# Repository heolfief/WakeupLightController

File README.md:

# WakeupLightController
**[THIS IS AN ABORTED WORK (lack of time to finish it)]**

This is a credit-card sized board designed to control LEDs (for example LED strip) as a wake-up light.

## What it does
The controller function in two modes :
* **Fade lamp**, LED intensity is controlled by an external potentiometer
* Parametric Progressive **wake-up light**

Wake-up times can be set by the dedicated **bluetooth android app**, and can be set for the week.
For example you can set the light to wake you up at half past 8 on Monday and at 12 on Sunday.

You can **enable or disable alarm** for **each day** with the app, or you can **manually disable all alarms** with an external **switch**.

When a alarm time approaches, the lamp will start to **fade-in linearly** and will be at **full intensity** when alarm time is reached.
The **duration** of the fade-in **can be set** via the app.

The board will **keep alarm settings** until new one are set, **even if power goes down**.

## How it works

The board is based on an **AVR microcontroller** (ATmega328p), a **bluetooth serial module** (HC-05), and a **real time clock** (DS3231).
The MCU is programmed in **C** within the **Atmel Studio 7** environment.

The real time clock is **extremely acurate** and will only drift few second per year. It is used to keep track of time to trigger alarms.

The bluetooth module is used to **pair an android device** with the board, and to send and get settings from a user.

The programm is composed of a main **state machine** and **run by interrupts**.

The **LED intensity** is controlled by a **16bits PWM**. As the ADC is only 10bits, when using the board as a lamp with a potentiommeter, LED intensity will only be controlled with a 10 bit resolution. That mean it as **1024 intensity steps** which is enough for most applications. However, when using the wake-up function, the LED intensity will be controlled by a 16bit resolution (**65536 steps**) which is good for a **very slow fade**.

**Brightness intensity** is **automaticaly compensated** to be seen as **linear by the human eye**.

**Settings are kept** even if power goes off by writing them to the **EEPROM**.

## Wiring

#### What you will need to connect to the board :
* A **12v** power source capable to deliver current for your LED setup + 200mA (max) for the board.
* **LEDs**, for example an LED strip. The board is thermally capable of delivering up to **4A** of current.
* A **potentiometer** (1 to 100k linear). You can use a rotary or a linear one.
* A **momentary button** for bluetooth pairing.  
* A **switch** if you want to add a way to manualy disable all alarms (even if they are enabled by the app).

Connection to the board are made by screwing cables to the screw terminals following this pinout diagram :

#### List of pins
* **GND**: Ground (0V) connection
* **+12V in**: Input for the 12V power source
* **+5V out**: Output to connect to pin 3 of potentiometer
* **POT**: Potentiometer wiper (pin 2) input
* **GND**: Ground (0V) connection for pin 1 of potentiometer
* **LED +**: LED anode (+) connection
* **LED -**: LED cathode (-) connection
* **Alarm sw.**: Switch input (switch connect the input to GND when turned on, floating when off) for disabling alarms
* **Pair/stop bt.**: Bluetooth pairing and alarm stop button (button connect the input to GND when turned on, floating when off)

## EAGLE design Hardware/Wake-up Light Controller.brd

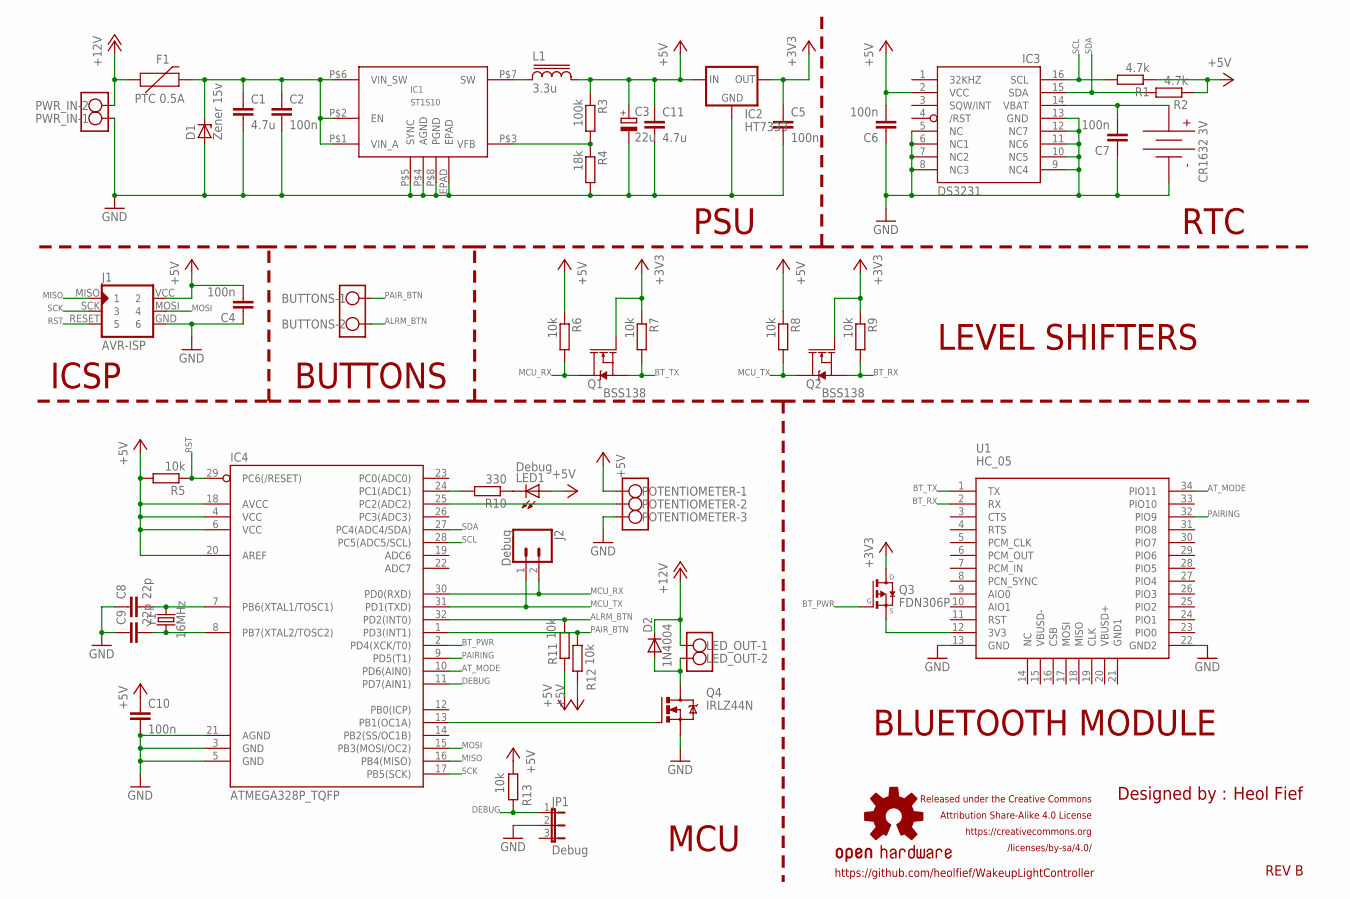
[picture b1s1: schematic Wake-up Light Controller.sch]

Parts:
BUTTONS: W237-102
C1, C11: 4.7u; C0805
C2, C4, C5, C6, C7, C10: 100n; C0805
C3: 22u; 153CLV-0405
C8, C9: 22p; C0805
D1: Zener 15v; SOD80C
D2: 1N4004; DO-214AC
F1: PTC 0.5A; PTH
IC1: ST1S10
IC2: HT7333; SOT-89
IC3: DS3231/SO; SO16W
IC4: ATMEGA328P_TQFP; TQFP32-08
J1: AVR-ISP; AVR-ISP-6PIN-SMAILL-SILK
J2: Debug; 1X02_NO_SILK
J3: CR1632_3V; BATTCON_16MM_PTH
JP1: Debug; JP2
L1: 3.3u; 74437346068
LED1: Debug; CHIPLED_1206
LED_OUT: W237-102
LOGO1: OSHW-LOGOM-COPPER; OSHW-LOGO-M_COPPER
POTENTIOMETER: W237-103
PWR_IN: W237-102
Q1, Q2: BSS138; SOT23-3
Q3: FDN306P; SSOT-3
Q4: IRLZ44N; TO220BH
R1, R2: 4.7k; M0805
R3: 100k; M0805
R4: 18k; M0805
R5, R6, R7, R8, R9, R11, R12, R13: 10k; M0805
R10: 330; M0805
U1: HC_05; BLUETOOTH_SMD
Y1: 16MHz; CRYSTAL-SMD-3.2X2.5MM

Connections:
+3V3: C5.1, IC2.1 (OUT), Q1.1 (G), Q2.1 (G), Q3.3 (D), R7.1, R9.1
+5V: C3.+, C4.2, C6.2, C10.1, C11.1, IC2.3 (IN), IC2.4 (IN), IC3.2 (VCC), IC4.4 (VCC), IC4.6 (VCC), IC4.18 (AVCC), IC4.20 (AREF), J1.VCC (2), L1.2, LED1.A, POTENTIOMETER.1, R1.1, R2.1, R3.1, R5.2, R6.1, R8.1, R11.1, R12.1, R13.2
+12V: D2.C, F1.P$1 (1), LED_OUT.1, PWR_IN.2
ALRM_BTN: BUTTONS.2, IC4.32 (PD2(INT0)), R11.2
AT_MODE: IC4.10 (PD6(AIN0)), U1.34 (PIO11)
BT_PWR: IC4.2 (PD4(XCK/T0)), Q3.1 (G)
BT_RX: Q2.2 (S), R9.2, U1.2 (RX)
BT_TX: Q1.2 (S), R7.2, U1.1 (TX)
DEBUG: IC4.11 (PD7(AIN1)), JP1.1, R13.1
GND: C1.2, C2.2, C3.-, C4.1, C5.2, C6.1, C7.1, C8.1, C9.1, C10.2, C11.2, D1.A, IC1.EPAD, IC1.P$4 (AGND), IC1.P$5 (SYNC), IC1.P$8 (PGND), IC2.2 (GND), IC3.5 (NC), IC3.6 (NC1), IC3.7 (NC2), IC3.8 (NC3), IC3.9 (NC4), IC3.10 (NC5), IC3.11 (NC6), IC3.12 (NC7), IC3.13 (GND), IC4.3 (GND), IC4.5 (GND), IC4.21 (AGND), J1.GND (6), J3.GND, JP1.2, POTENTIOMETER.3, PWR_IN.1, Q4.S, R4.2, U1.13 (GND), U1.22 (GND2)
MCU_RX: IC4.30 (PD0(RXD)), J2.2, Q1.3 (D), R6.2
MCU_TX: IC4.31 (PD1(TXD)), J2.1, Q2.3 (D), R8.2
MISO: IC4.16 (PB4(MISO)), J1.MISO (1)
MOSI: IC4.15 (PB3(MOSI/OC2)), J1.MOSI (4)
unnamed: D2.A, LED_OUT.2, Q4.D
unnamed: C8.2, IC4.7 (PB6(XTAL1/TOSC1)), Y1.3 (2)
unnamed: IC4.24 (PC1(ADC1)), R10.2
unnamed: C9.2, IC4.8 (PB7(XTAL2/TOSC2)), Y1.1
unnamed: Q3.2 (S), U1.12 (3V3)
unnamed: IC1.P$7 (SW), L1.1
unnamed: IC1.P$3 (VFB), R3.2, R4.1
unnamed: LED1.C, R10.1
unnamed: C1.1, C2.1, D1.C, F1.P$2 (2), IC1.P$1 (VIN_A), IC1.P$2 (EN), IC1.P$6 (VIN_SW)
unnamed: IC4.13 (PB1(OC1A)), Q4.G
unnamed: IC4.25 (PC2(ADC2)), POTENTIOMETER.2
PAIRING: IC4.9 (PD5(T1)), U1.32 (PIO9)
PAIR_BTN: BUTTONS.1, IC4.1 (PD3(INT1)), R12.2
RST: IC4.29 (PC6(/RESET)), J1.RESET (5), R5.1
SCK: IC4.17 (PB5(SCK)), J1.SCK (3)
SCL: IC3.16 (SCL), IC4.28 (PC5(ADC5/SCL)), R1.2
SDA: IC3.15 (SDA), IC4.27 (PC4(ADC4/SDA)), R2.2
VBAT: C7.2, IC3.14 (VBAT), J3.VCC@1 (VCC), J3.VCC@2 (VCC)

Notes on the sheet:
PSU
ICSP
MCU
REV B
Heol Fief
Designed by :
Released under the Creative Commons Attribution Share-Alike 4.0 License https://creativecommons.org /licenses/by-sa/4.0/
BLUETOOTH MODULE
RTC
BUTTONS
LEVEL SHIFTERS
CR1632 3V
https://github.com/heolfief/WakeupLightController

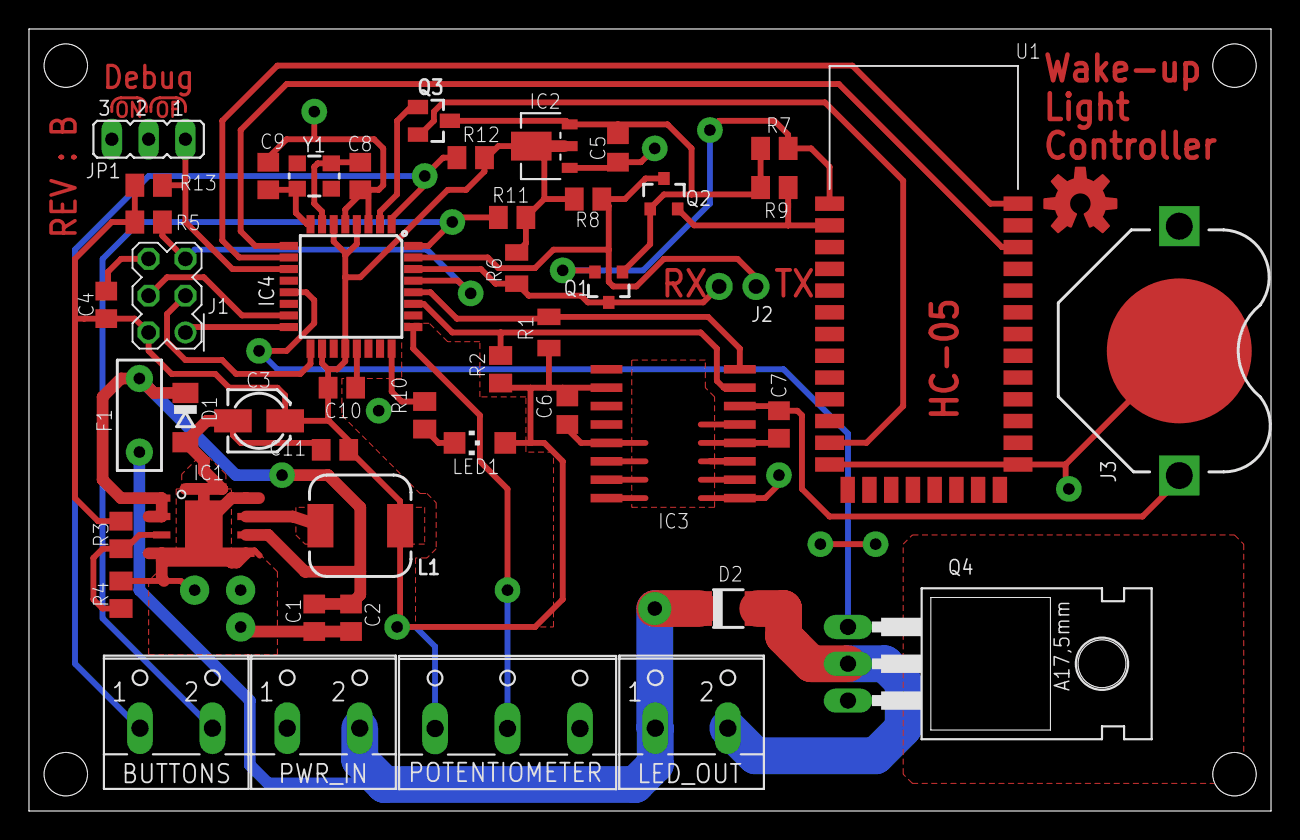
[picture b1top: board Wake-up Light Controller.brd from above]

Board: 2 copper layers, 85.7 x 54.0 mm, 48 parts (0 on the bottom side), 32 nets.

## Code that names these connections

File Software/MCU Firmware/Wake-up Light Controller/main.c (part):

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
// Hardware related constants//////////////////////////////
#define F_CPU			16000000UL						// 16MHz external oscillator
#define BT_PWR			PD4								// ...
#define AT_MODE			PD6								// ...
#define ALRM_BTN		PD2								// ...
#define PAIR_BTN		PD3								// ...
#define PAIR_INFO		PD5								// ...
#define DEBUG_JUMPER	PD7								// ...
#define DEBUG_LED		PC1								// ... Define IOs

// Software related constants//////////////////////////////
#define ALRM_EN			1								// ...
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
// User definable constants///////////////////////////////
#define PAIR_NAME	"Wake up light"						// Name of the bluetooth device, change it to whatever you like (Max 20 characters)
#define PAIR_PIN	"1234"								// Password of the bluetooth device pairing, change it to whatever you like
#define OFFTHRESHOLD 2									// Threshold (10 bit value) for potentiometer to be read as 0 (lamp off) to compensate for noise

// Libraries used/////////////////////////////////////////
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	DDRD &= ~((1<<PAIR_INFO) | (1<<ALRM_BTN));			// PAIR_INFO and ALRM_BTN as inputs
	DDRD |= (1<<BT_PWR) | (1<<AT_MODE);					// BT_PWR and AT_MODE as outputs
	DDRD &= ~((1<<ALRM_BTN) | (1<<PAIR_BTN) | (1<<DEBUG_JUMPER));// Alarm and pair buttons as inputs, debug jumper as input
	DDRB |= (1<<PB1);									// PB1 (OSC1A) as output
	PORTC |= (1<<DEBUG_LED);							// DEBUG_LED off
	PORTD |= (1<<BT_PWR);								// High level (BT module off)
	PORTD &= ~(1<<AT_MODE);								// Low level
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	PORTD |= (1<<ALRM_BTN) | (1<<PAIR_BTN) | (1<<DEBUG_JUMPER);	// Enable (weak) internals pullups

	PCICR |= (1<<PCIE2);								// Enable pin change interrupts
	PCMSK2 |= (1<<PCINT21);								// Enable pin change interrupt 21 (connected to pairing pin of bluetooth module)

	EIMSK |= (1<<INT1);									// Enable external interrupt INT1
	EICRA |= (1<<ISC11);								// ...
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	UART_transmit_String("\r\n");						// Send carriage return and new line

	UART_transmit_String("AT+PSWD=");					// ...
	UART_transmit_String(PAIR_PIN);						// ... Change the bluetooth pairing password
	UART_transmit_String("\r\n");						// Send carriage return and new line

	_delay_ms(200);										// Wait for bluetooth module to stop communicate
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		alarm_start_time_calculation();					// Calculate start time of alarm based on alarm duration
		TIMSK1 |= (1<<TOIE1);							// Enable interrupt on timer 1 overflow

		if(bit_is_set(PIND, DEBUG_JUMPER))debug();		// If jumper is removed, go to debug mode
		sei();											// Global interrupts enable
		state = STANDBY;								// After initialization done, got to standby state
		break;
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		UCSR0B |= ((1<<RXCIE0) | (1<<TXCIE0));			// Enable RX and TX interrupts
		while (is_paired);								// Wait for bluetooth communication complete					// TO IMPROVE
		UCSR0B &= ~((1<<RXCIE0) | (1<<TXCIE0));			// Disable RX and TX interrupts
		pair_request_flag = 0;							// Pairing complete
		PORTD |= (1<<BT_PWR);							// Cut power to bluetooth module*/
		state = STANDBY;								// Go to standby state
		break;
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		actual_day = rtc_get_day();						// Get day from RTC Monday is 0 (RTC return 1 for Monday)
		alarm_start_time_calculation();					// Calculate start time of alarm based on alarm duration
	}
	if((alarm_in_process == 0) && (actual_hour == alrm_start_hr[actual_day]) && (actual_min == alrm_start_min[actual_day]) && (alrm_EN[actual_day] == 1) && (bit_is_set(PIND, ALRM_BTN)) && (actual_sec == 0))
	// If alarm time is reached and no alarm is in process and alarm is enabled by software and hardware
	{
		alarm_in_process = 1;							// Set the flag
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
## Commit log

2017-08-26 Create newfolder
2017-08-30 Correct errors
2017-08-30 Add hardware Eagle files
2017-08-30 Add bold formating
2017-08-30 Correct spelling
2017-08-30 Add tab width formating
2017-09-01 Place silkscreen
    Place silkscreen, and change i2c pullups to 4.7k ohm
2017-09-01 Add software files
2017-09-01 Reshaped one trace
2017-09-01 Mention MCU brand
2017-09-02 Mention I2C lib credentials
2017-09-02 Add INT1 declarations
2017-09-04 Add schematics pdf
2017-09-04 Add 3D board render for readme.md
2017-09-04 Add pinout diagram
2017-09-04 Explain pinout
2017-09-04 Bold pin names
2017-09-05 Group ISRs and remove reset loop of OCR1A
2017-09-07 Changed state name
    Changed PAIR state to BLUETOOTH state
2017-09-07 Add comments on INIT state
2017-09-07 Add return to standby state after bt transmission complete
2017-09-07 Add states flowchart
2017-09-07 Change mismatched variables
2017-09-07 Host picture on noelshack.com instead of github
2017-09-10 Removed soft-powered RTC
    RTC is now hard-powered (directly powered on PCB)
2017-09-10 Add debug funtion
2017-09-10 REV B
    Add debug function,
    Add RTC battery,
    Changed global layout
2017-09-14 Add PTC fuse on 12V input
2017-09-14 Modify copper trace
2017-09-15 Changed variable name
2017-09-15 Add linear brightness conversion to alarm
2017-09-17 Add overvoltage protection
2017-09-17 Change diodes names
2017-09-17 Changed resistor pad spacing
2017-09-17 Move via
2017-09-17 Changed battery holder name
2017-09-21 Changed inductor package
2017-10-01 Update pinout diagram
2017-10-01 Modify copper traces
2017-10-08 Add bluetooth data serial frame
2017-10-17 Isolate ADC trace from switching PSU
2017-10-18 Optimize layout
2017-10-22 Change text size
2017-10-31 Add filtering cap, tweak layout
2017-10-31 test
2017-10-31 Resolve Git config `ui = always` breaks diff pane issue
2017-10-31 Formating
2017-11-01 Changed component value
    Add jumper value "debug"
2017-11-01 Changed component value
    Add "debug" value to jumper JP1
2017-11-01 Add Android App files, + folders cleanup
2017-11-01 Fix apk instal crash due to too large icon file
2017-11-02 Fix display bug
2017-11-12 Add set day of week function
2017-11-12 Correct misspelling
2017-11-12 Add weekday settings function
2019-01-17 Bug patch
2020-03-12 Add stripped down version, just uses PWM (lamp only, no wake up)
2020-03-13 Update code : use exp instead of pow

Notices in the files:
Software/MCU Firmware/Wake-up Light Controller/main.c:
This Software is released under the Creative Commons Attribution Share-Alike 4.0 License
parts and their libraries:
SparkFun-Aesthetics: Licensing: Creative Commons ShareAlike 4.0 International - https://creativecommons.org/licenses/by-sa/4.0
inductor-wurth: Copyright (C) 2010, Bob Starr
